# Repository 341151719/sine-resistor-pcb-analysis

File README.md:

# 正弦电阻 / Active Acoustic Impedance Controller

这是 PCB 修正、SPICE 分析和故障排查的审计仓库。仓库的目的，是让每次
电路修改、仿真假设和判断都能通过 Git 提交记录追溯；它不是已经通过生产
签核的最终硬件发布包。

## 先看什么

0. [新板从验收到初步改板操作手册](新板从验收到初步改板操作手册.md)：按新板版本确认、断电检查、基本上电、固件编写/烧录、问题复现和可逆改板的顺序执行。
1. [2026-09-15 实验还原证据复核](实验还原部分/主动审计/EVIDENCE_REASSESSMENT_20260915.md)：修正峰值电流与持续CC混淆，同步H07/H08状态，补充较大启动扰动验证。
2. [V8 KiCad 修正版](KICAD部分/正弦电阻V8_KiCad10.0.4_稳定性修正版_2026-09-04/)
   及其 [修改说明](KICAD部分/正弦电阻V8_KiCad10.0.4_稳定性修正版_2026-09-04/RELEASE_NOTES_V8.md)。
3. [V7 加工基线](KICAD部分/给厂商的板子加工数据/正弦电阻V7_KiCad10.0.4_校正转换版/)。
4. [SPICE 验证报告](SPICE部分/VALIDATION_REPORT_20260904.md) 和
   [实际问题记录](实际遇到的问题/)。
5. [故障假设排查总表](故障假设排查_20260908/假设总表.md)：H01–H11 记录
   单一加工/参数错误审计；H12 新增 OPA548 E/S–R5 组合动态机制审计。
6. [实验还原与可复现证据](实验还原部分/)：实板实验记录、早期错误复现和
   对既有 SPICE/KiCad 检查盲区的主动审计。

## 当前诊断状态（2026-09-08）

后续状态更新（2026-09-15）：H07修正版的3个固定偏置案例均完成且未复现目标，但不覆盖上电过程；
H08修正版未复现，但使用V8的C27值。OPA ON案例的约69 mA峰值不构成持续70 mA CC验证。
以下段落保留2026-09-08的模型结论，具体有效性以最新证据复核和更新后的假设总表为准。

官方 OPA548/OPA1656 模型在正确的 PSpice 兼容设置下可以运行。H12 进一步
解除此前“OPA548 固定 OFF”的假设，并加入 R10/TLP185、有限 E/S 状态和
J1/PGND 非理想项。23 组机制扫描没有自然产生 100--110 kHz；但当 OPA548
进入 ON 时，全官方模型出现约 453 kHz 的 U4B–R5–OPA548 组合模态，且把
R5 近似拆除后该模态消失。TP8 只有约 56 µVpp，因此仍不能解释实板上
100--110 kHz、超过 10 Vpp 的目标波形。H01–H11 的单点排查结论保持不变；
“本模型未复现”不等于已排除实物器件损坏、多故障叠加或未建模动态。

## 目录

| 目录 | 内容 |
|---|---|
| `KICAD部分/` | V7/V8 原理图、PCB、封装表、加工输出和验证记录 |
| `SPICE部分/` | SPICE 源模型、网表、脚本和历史验证报告 |
| `实际遇到的问题/` | 实测现象、局部网表和根因判定计划 |
| `故障假设排查_20260908/` | 每个假设独立存档的预测、deck、log 和审查 |
| `实验还原部分/` | 经整理的实板记录、可运行复现 deck 和主动审计脚本 |

## 复现约定

仿真通常使用 ngspice-42；TI PSpice 宏模型需要 `set ngbehavior=ps`，并且
某些官方模型需要显式 `TEMP`。每个故障目录都记录了实际命令和模型限制。
历史网表中可能保留当时机器的绝对路径，这是审计记录的一部分；在新机器
上运行前应根据目录位置调整 `.include` 路径。`.dat` 波形文件和环境安装包
没有纳入 Git，它们可由网表重新生成，避免仓库膨胀。

## 版本纪律

V7 目录作为原始加工基线保留；V8 是当前修正版工作状态，不应在没有新的
验证记录时覆盖。请用独立提交记录新的板改动、仿真假设和结论，并在
`CHANGELOG.md` 中补充面向人的摘要。

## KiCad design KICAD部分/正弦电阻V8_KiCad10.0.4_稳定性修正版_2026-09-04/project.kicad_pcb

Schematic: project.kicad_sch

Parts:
C1, C2: 10uF; C0805; LCSC Part # C15850
C3, C9, C10, C15, C16, C18, C19, C20, C21, C22, C26: 100nF; C0805; LCSC Part # C49678
C4: 47nF; C0805; LCSC Part # C1845663
C5, C6: 470uF; CAP-SMD_BD10.0-L10.3-W10.3-LS11.3-FD; Manufacturer Part XT470UF35V90RV0080; LCSC Part Name 470uF ±20% 35V
C7, C8: 100nF; C0805; Manufacturer Part CC0805KRX7R9BB104; LCSC Part Name 100nF ±10% 50V
C11, C12, C25, C28: 1uF; C0805; LCSC Part # C344178
C13, C14: 1p/2.2p/4.7p EXP; C0805; not fitted
C17: 10nF; C0805; LCSC Part # C342877
C23: 220nF; C0805; LCSC Part # C45359963
C24: 4.7uF; C0805; LCSC Part # C380342
C27: 10nF; C0805; Manufacturer Part C0805C103J5GACTU; LCSC Part # C2167597
C29, C30: 1uF; C0805; not fitted
C31, C37: 4.7p; C0805; not fitted
C32, C38: 10p; C0805; not fitted
C33, C39: 22p; C0805; not fitted
C34, C40: 47p; C0805; not fitted
C35, C41: 100p; C0805; not fitted
C36, C42: 10p-100p; C0805; not fitted
D1, D2: SS56B; SMB_L4.3-W3.6-LS5.4-RD; LCSC Part # C14651
D3: SS56 +clamp SPK DNP; SMB_L4.3-W3.6-LS5.4-RD; not fitted
D4: SS56 -clamp SPK DNP; SMB_L4.3-W3.6-LS5.4-RD; not fitted
FB1, FB2, FB3: 150R@100MHz; L0805; LCSC Part # C139474
FRAME1: default841x594
J1, J2, J5, J6: WAGO 2060 3P; CONN-SMD_2060-453; Manufacturer Part 2060-453/998-404; LCSC Part Name 1x3P 4mm 每排P数:3 排数:1
J3, J9: WAGO 2060 2P; CONN-SMD_2060-452; Manufacturer Part 2060-452/998-404; LCSC Part Name 1x2P 4mm 每排P数:2 排数:1
J4: WAGO 2060 2P; CONN-SMD_2060-452; Manufacturer Part SPEAKER WAGO 2060 SMT 2P; LCSC Part Name 1x2P 4mm 每排P数:2 排数:1
J7: SWD bare SMT pads; AAI_C11_35_LOCAL_Footprints_AAI_PinHeader_1x05_P1_27mm_Vert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
J8: WAGO 2060 3P; CONN-SMD_2060-453; Manufacturer Part UART bare SMT pads; LCSC Part Name 1x3P 4mm 每排P数:3 排数:1
J10: EXP_SPI_TIM_DNP; AAI_C11_35_LOCAL_Footprints_AAI_PinHeader_1x05_P2_54mm_Vert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; not fitted
J11: EXP_I2C_DAC_DNP; AAI_C11_35_LOCAL_Footprints_AAI_PinHeader_1x05_P2_54mm_Vert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; not fitted
J12, J13: 1×5P 2.54mm母排; HDR-TH_5P-P2.54-V-F; Manufacturer Part 2.54-1*5P母; LCSC Part Name 1x5P 间距:2.54mm 直插
J14: WAGO 2060 1P; CONN-SMD_L12.7-W3.9_2060-451-998-404; Manufacturer Part 2060-451/998-404; LCSC Part Name 1x1P 每排P数:1 排数:1
R1, R2, R42, R43: 0R; R0805; not fitted
R3, R4, R17, R36, R46: 0R; R0805; LCSC Part # C17477
R5, R18: 100R; R0805; LCSC Part # C2988937
R6: 0R; R0805; Manufacturer Part 0805W8F0000T5E; LCSC Part Name 0Ω ±1% 125mW 厚膜电阻
R7: 57.6kR; R0805; LCSC Part # C5153977
R8: 33.2kR 1%; R0805; not fitted
R9: 22.1kR 1%; R0805; not fitted
R10: 6.8kR; R0805; Manufacturer Part 0805W8F6801T5E; LCSC Part # C17772
R11: 1kR; R0805; LCSC Part # C95781
R12: 4.7R 2W; AAI_R_2512_Production_4R7_2W; Manufacturer Part CRH2512F4R70E04S; LCSC Part # C2897629
R13, R15: 1.000kR; R0805; LCSC Part # C110774
R14: 49.9kR; R0805; LCSC Part # C1730568
R16: 39.0kR; R0805; LCSC Part # C1720356
R19: 30.9kR; R0805; LCSC Part # C865394
R20, R21, R22, R35: 10.0kR; R0805; LCSC Part # C110775
R23: 100kR; R0805; LCSC Part # C2907217
R24: 10kR; R0805; LCSC Part # C2907219
R25: 6.49kR 0.1%; R0805; not fitted
R26, R31: 10k; R0805; not fitted
R27, R30: 100k; R0805; not fitted
R28: 100kR ±1%; R0805; not fitted
R29: 10kR ±1%; R0805; not fitted
R32, R33: 360kR ±1%; R0805; not fitted
R34: 1.000MR; R0805; LCSC Part # C2075448
R37, R38, R40: 1MR; R0805; not fitted
R39: 10kR; R0805; not fitted
R41: 10MR; R0805; not fitted
R44, R45: 1k-10k; R0805; not fitted
RSH2: 0.100R; AAI_C11_35_LOCAL_Footprints_AAI_SHUNT_4T_3920_Kelvin; LCSC Part # C393067
TP1: TP1; AAI_C11_35_LOCAL_Footprints_AAI_TestPoint_THTPad_D1_5mm_Dri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
TP2: TP2; AAI_C11_35_LOCAL_Footprints_AAI_TestPoint_THTPad_D1_5mm_Dri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
TP3: SENSE_DRV; AAI_C11_35_LOCAL_Footprints_AAI_TestPoint_THTPad_D1_5mm_Dri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
TP4: SENSE_SPK; AAI_C11_35_LOCAL_Footprints_AAI_TestPoint_THTPad_D1_5mm_Dri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
TP5: TP5; AAI_C11_35_LOCAL_Footprints_AAI_TestPoint_THTPad_D1_5mm_Dri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
TP6: TP6; AAI_C11_35_LOCAL_Footprints_AAI_TestPoint_THTPad_D1_5mm_Dri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
TP7: TP7; AAI_C11_35_LOCAL_Footprints_AAI_TestPoint_THTPad_D1_5mm_Dri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
TP8: TP8; AAI_C11_35_LOCAL_Footprints_AAI_TestPoint_THTPad_D1_5mm_Dri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
TP9: TP9; AAI_C11_35_LOCAL_Footprints_AAI_TestPoint_THTPad_D1_5mm_Dri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
TP10: TP10; AAI_C11_35_LOCAL_Footprints_AAI_TestPoint_THTPad_D1_5mm_Dri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
TP11: TP11; AAI_C11_35_LOCAL_Footprints_AAI_TestPoint_THTPad_D1_5mm_Dri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
TP12: TP12; AAI_C11_35_LOCAL_Footprints_AAI_TestPoint_THTPad_D1_5mm_Dri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
TP13: TP13; AAI_C11_35_LOCAL_Footprints_AAI_TestPoint_THTPad_D1_5mm_Dri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
TP14: TP14; AAI_C11_35_LOCAL_Footprints_AAI_TestPoint_THTPad_D1_5mm_Dri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
TP15: TP15; AAI_C11_35_LOCAL_Footprints_AAI_TestPoint_THTPad_D1_5mm_Dri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
TP16: TP16; AAI_C11_35_LOCAL_Footprints_AAI_TestPoint_THTPad_D1_5mm_Dri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
TP17: TP17; AAI_C11_35_LOCAL_Footprints_AAI_TestPoint_THTPad_D1_5mm_Dri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
TP18: TP_VSENSE_RAW; AAI_C11_35_LOCAL_Footprints_AAI_TestPoint_THTPad_D1_5mm_Dri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
TP19: TP_AD633_Z; AAI_C11_35_LOCAL_Footprints_AAI_TestPoint_THTPad_D1_5mm_Dri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
TP20: TP_IPORT; AAI_C11_35_LOCAL_Footprints_AAI_TestPoint_THTPad_D1_5mm_Dri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
TP21: Test-Point-0.5mm
U1: OPA548F/500; TO-263-7_L10.2-W10.4-P1.27-LS14.4-TL; Manufacturer Part OPA548F/500; LCSC Part Name 高压、大电流运算放大器
U2: AD633ARZ-R7; SOIC-8_L4.9-W3.9-P1.27-LS6.0-BL; Manufacturer Part AD633ARZ-R7; LCSC Part Name 四象限模拟乘法器
U3: INA149AIDR; SOIC-8_L4.9-W3.9-P1.27-LS6.0-BL; Manufacturer Part INA149AIDR; LCSC Part Name 高共模电压差分放大器
U4, U8: OPA1656IDR; SOIC-8_L4.9-W3.9-P1.27-LS6.0-BL; Manufacturer Part OPA1656IDR; LCSC Part Name 超低噪声、低失真、FET输入音频运算放大器
U5: STM32G431CBT6; LQFP-48_L7.0-W7.0-P0.50-LS9.0-BL; Manufacturer Part STM32G431CBT6; LCSC Part Name 带DSP和FPU的170MHz主流ARM Cortex-M4 MCU，具有12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
U6: AMS1117-3.3; SOT-223-3_L6.5-W3.4-P2.30-LS7.0-BR; LCSC Part # C6186
U7: TLP185(GR-TPR,E; SOP-6_4P-L3.7-W4.6-P2.54-LS7.0-BL; Manufacturer Part TLP185(GR-TPR,E; LCSC Part Name DC输入 隔离电压(rms):3750V
U9: OPA1656IDR; SOIC-8_L4.9-W3.9-P1.27-LS6.0-BL; not fitted
U10: TMUX7219DGKRQ1; VSSOP-8_L3.0-W3.0-P0.65-LS4.9-BL; not fitted

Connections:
$1N56724: U9.6 (-INB), U9.7 (OUTB)
$1N56728: R23.2, TP21.1, U10.5 (EN)
AD633_Z: R36.1, R37.2, R38.2, TP19.1, U2.4 (Z)
ADC_ISIG: R27.2, U5.8 (PA0)
ADC_PWR_N: R30.2, R31.1, U5.11 (PA3)
ADC_PWR_P: R28.2, R29.1, U5.10 (PA2)
ADC_SPK: R25.2, R26.1, U5.9 (PA1)
ADC_TEMP: J13.4, U5.16 (PB0)
AGND: C9.2, C10.2, C11.2, C12.2, C15.2, C16.2, C17.2, C18.2, C22.2, C23.2, C25.2, C28.2, C29.2, J2.2, J6.2, R3.2, R4.1, R13.2, R15.2, R20.2, R26.2, R36.2, R43.2, TP16.1, U2.2 (Y2), U2.8 (X2), U3.1 (REFB), U3.5 (REFA), U5.19 (VSSA), U9.3 (+INA), U9.5 (+INB), U10.3 (GND), U10.6 (SEL), U10.8 (S2)
ANA_N: C10.1, C12.1, C16.1, FB2.2, TP12.1, U2.3 (-VS), U3.4 (V-), U4.4 (V-), U8.4 (V-), U9.4 (V-), U10.7 (VSS)
ANA_N_EXT: FB2.1, J2.3, R2.2
ANA_P: C9.1, C11.1, C15.1, FB1.2, J6.3, TP11.1, U2.6 (+VS), U3.7 (V+), U4.8 (V+), U8.8 (V+), U9.8 (V+), U10.4 (VDD)
ANA_P_EXT: FB1.1, J2.1, R1.2
DAC_AUX_RAW: J11.5, R35.1, U5.13 (PA5)
DAC_BUF: R17.1, U8.1 (OUTA), U8.5 (+INB)
DAC_BUF_N: R17.2, U8.2 (-INA)
DAC_R_FILT: C17.1, R18.2, U8.3 (+INA)
DAC_R_RAW: R18.1, U5.12 (PA4)
DGND: C1.2, C2.2, C3.2, C19.2, C20.2, C21.2, C24.2, C26.2, J3.2, J7.5, J8.3, J9.2, J11.2, J13.5, R4.2, R29.2, R31.2, U5.23 (VSS), U5.35 (VSS), U5.47 (VSS), U6.1 (ADJ(GND)), U7.3 (CAT)
DRV: D1.2 (A), D2.1 (K), R12.1, R46.2, RSH2.1 (FORCE_DRV), TP2.1
FAULT_IN: J9.1, U5.17 (PB1)
GPIO_SPARE1: J12.1, U5.15 (PA7)
GPIO_SPARE2: J12.2, U5.22 (PB10)
GPIO_SPARE3: J12.3, U5.29 (PB15)
GPIO_SPARE4: J12.4, U5.28 (PB14)
GPIO_SPARE5: J12.5, U5.27 (PB13)
GPIO_SPARE6: J13.1, U5.26 (PB12)
GPIO_SPARE7: J13.2, U5.25 (PB11)
GPIO_SPARE8: J13.3, U5.46 (PB9)
I2C_SCL: J11.3, R33.1, U5.45 (PB8-BOOT0)
I2C_SDA: J11.4, R32.1, U5.44 (PB7)
ILIM_SET: R7.1, R8.1, R9.1, TP10.1, U1.3 (ILIM)
IPORT: C29.1, R39.2, R40.1, TP20.1
ISIG: C13.1, C31.1, C32.1, C33.1, C34.1, C35.1, R14.1, R27.1, R39.1, R44.1, TP5.1, U2.7 (X1), U4.1 (OUTA)
ISIG_TRIM: C28.1, R34.1, R35.2
MCU_OPA_EN: R11.1, U5.14 (PA6)
MUL_RAW: TP7.1, U2.5 (W), U4.5 (+INB)
NRST: C26.1, J7.4, R24.1, U5.7 (PG10-NRST)
OPA_EN_LED_A: R11.2, U7.1 (AN)
OPA_ES: R10.1, TP9.1, U1.7 (E/S), U7.4 (EMI)
OPA_IN_N: R6.2, U1.2 (VIN-)
OPA_IN_P: R5.2, U1.1 (VIN+)
OPA_OUT: R46.1, U1.6 (VO)
PGND: C4.2, C5.1, C6.2, C7.2, C8.1, J1.2, J4.2, R3.1, TP17.1
PWR_N: C6.1, C8.2, C27.2, D2.2 (A), D4.2 (A), J1.3, R2.1, R7.2, R8.2, R9.2, R10.2, R30.1, TP14.1, U1.4 (V-), U1.8 (V-)
PWR_P: C5.2, C7.1, C27.1, D1.1 (K), D3.1 (K), J1.1, R1.1, R28.1, TP13.1, U1.5 (V+), U7.6 (COL)
SENSE_DRV: RSH2.3 (SENSE_DRV), TP3.1, U3.2 (IN-)
SENSE_SPK: RSH2.4 (SENSE_SPK), TP4.1, U3.3 (IN+)
SERVO_INT_N: C30.2, R40.2, R41.2, R42.2, U9.2 (-INA), U10.2 (S1)
SNUB_MID: C4.1, R12.2
SPI_MISO: J10.3, U5.41 (PB4)
SPI_MOSI: J10.4, U5.42 (PB5)
SPI_NSS: J10.1, U5.39 (PA15)
SPI_SCK: J10.2, U5.40 (PB3)
SPK: D3.2 (A), D4.1 (K), J4.1, R6.1, R25.1, RSH2.2 (FORCE_SPK), TP1.1
SWCLK: J7.3, U5.38 (PA14)
SWDIO: J7.2, U5.37 (PA13)
TIM_SYNC: J10.5, U5.30 (PA8)
U4A_LEAD_MID: C36.1, R44.2
U4A_N: C13.2, C31.2, C32.2, C33.2, C34.2, C35.2, C36.2, R13.1, R14.2, R34.2, U4.2 (-INA)
U4B_LEAD_MID: C42.1, R45.2
U4B_N: C14.2, C37.2, C38.2, C39.2, C40.2, C41.2, C42.2, R15.1, R16.2, U4.6 (-INB)
UART_RX: J8.2, U5.32 (PA10)
UART_TX: J8.1, U5.31 (PA9)
V3V3: C2.1, C3.1, C19.1, C20.1, C21.1, C24.1, FB3.1, J7.1, J11.1, R23.1, R24.2, R32.2, R33.2, TP15.1, U5.1 (VBAT), U5.24 (VDD), U5.36 (VDD), U5.48 (VDD), U6.2 (VOUT), U6.4 (VOUT)
V3V3A: C22.1, C23.1, C25.1, FB3.2, R19.1, U5.20 (VREF+), U5.21 (VDDA)
V5_IN: C1.1, J3.1, U6.3 (VIN)
VCMD: C14.1, C37.1, C38.1, C39.1, C40.1, C41.1, R5.1, R16.1, R45.1, TP8.1, U4.7 (OUTB)
VK: J5.2, TP6.1, U2.1 (Y1)
VK_AMP_N: R21.1, R22.2, U8.6 (-INB)
VK_EXT: J5.3, J6.1
VK_MCU: J5.1, R22.1, U8.7 (OUTB)
VREF_0V477: C18.1, R19.2, R20.1, R21.2
VSENSE_RAW: TP18.1, U3.6 (VOUT), U4.3 (+INA)
ZSERVO_OUT: C30.1, R38.1, R41.1, R42.1, R43.1, U9.1 (OUTA), U10.1 (D)
ZTRIM: J14.1, J14.2, R37.1

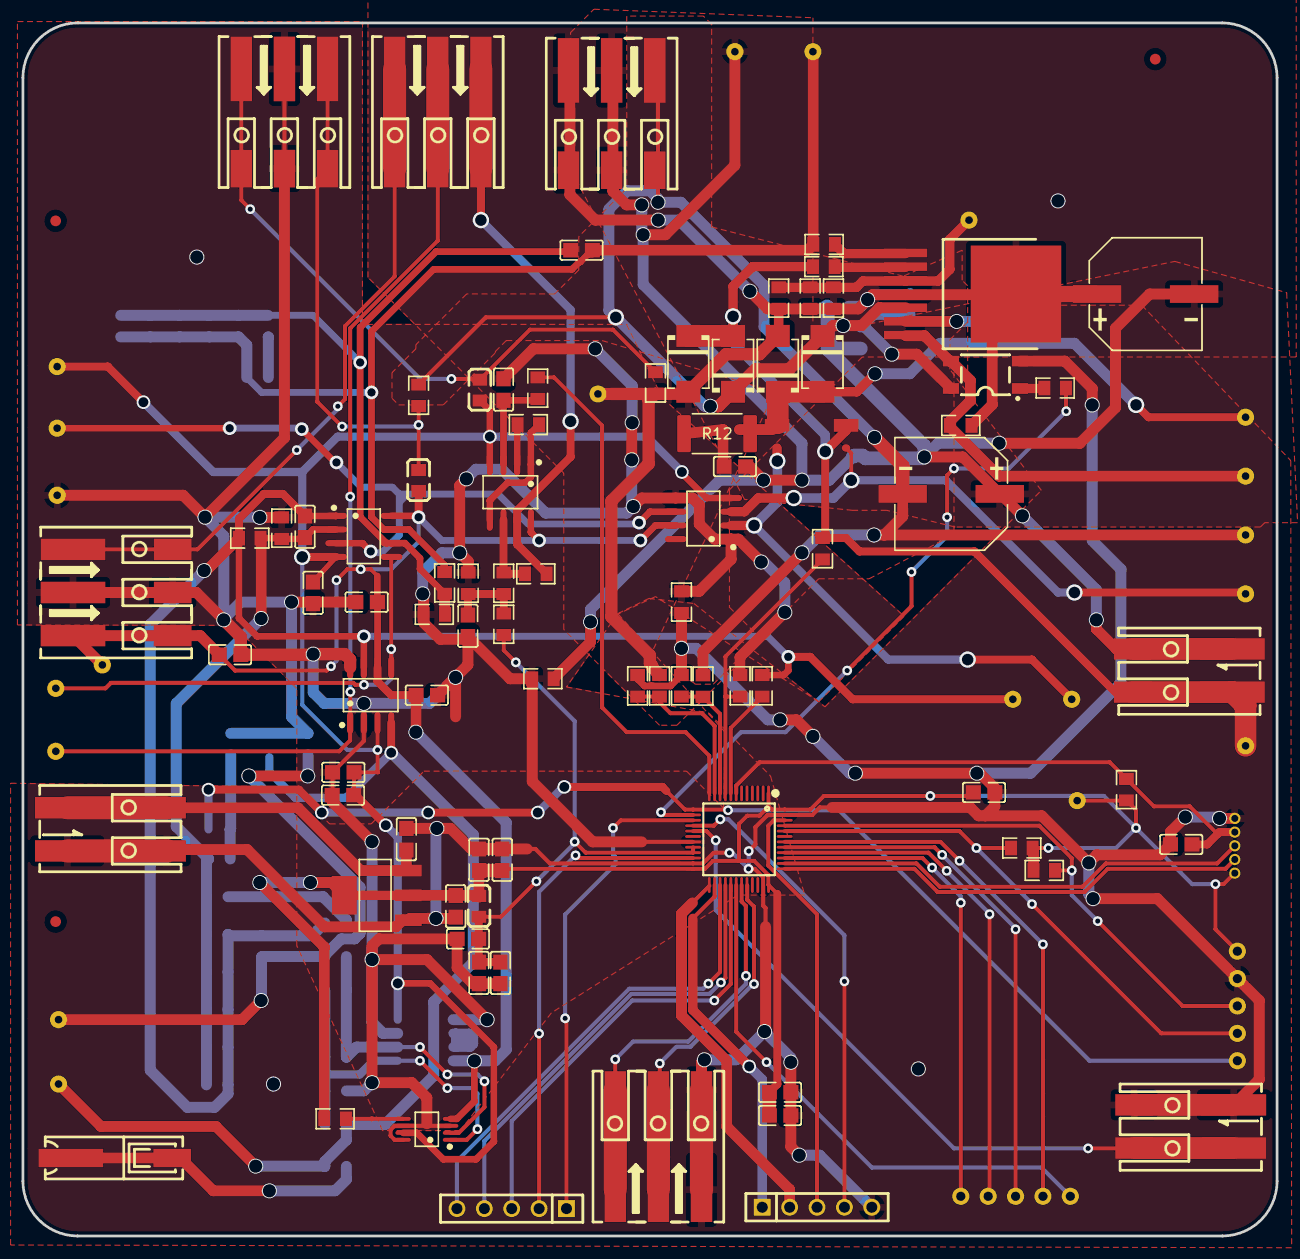
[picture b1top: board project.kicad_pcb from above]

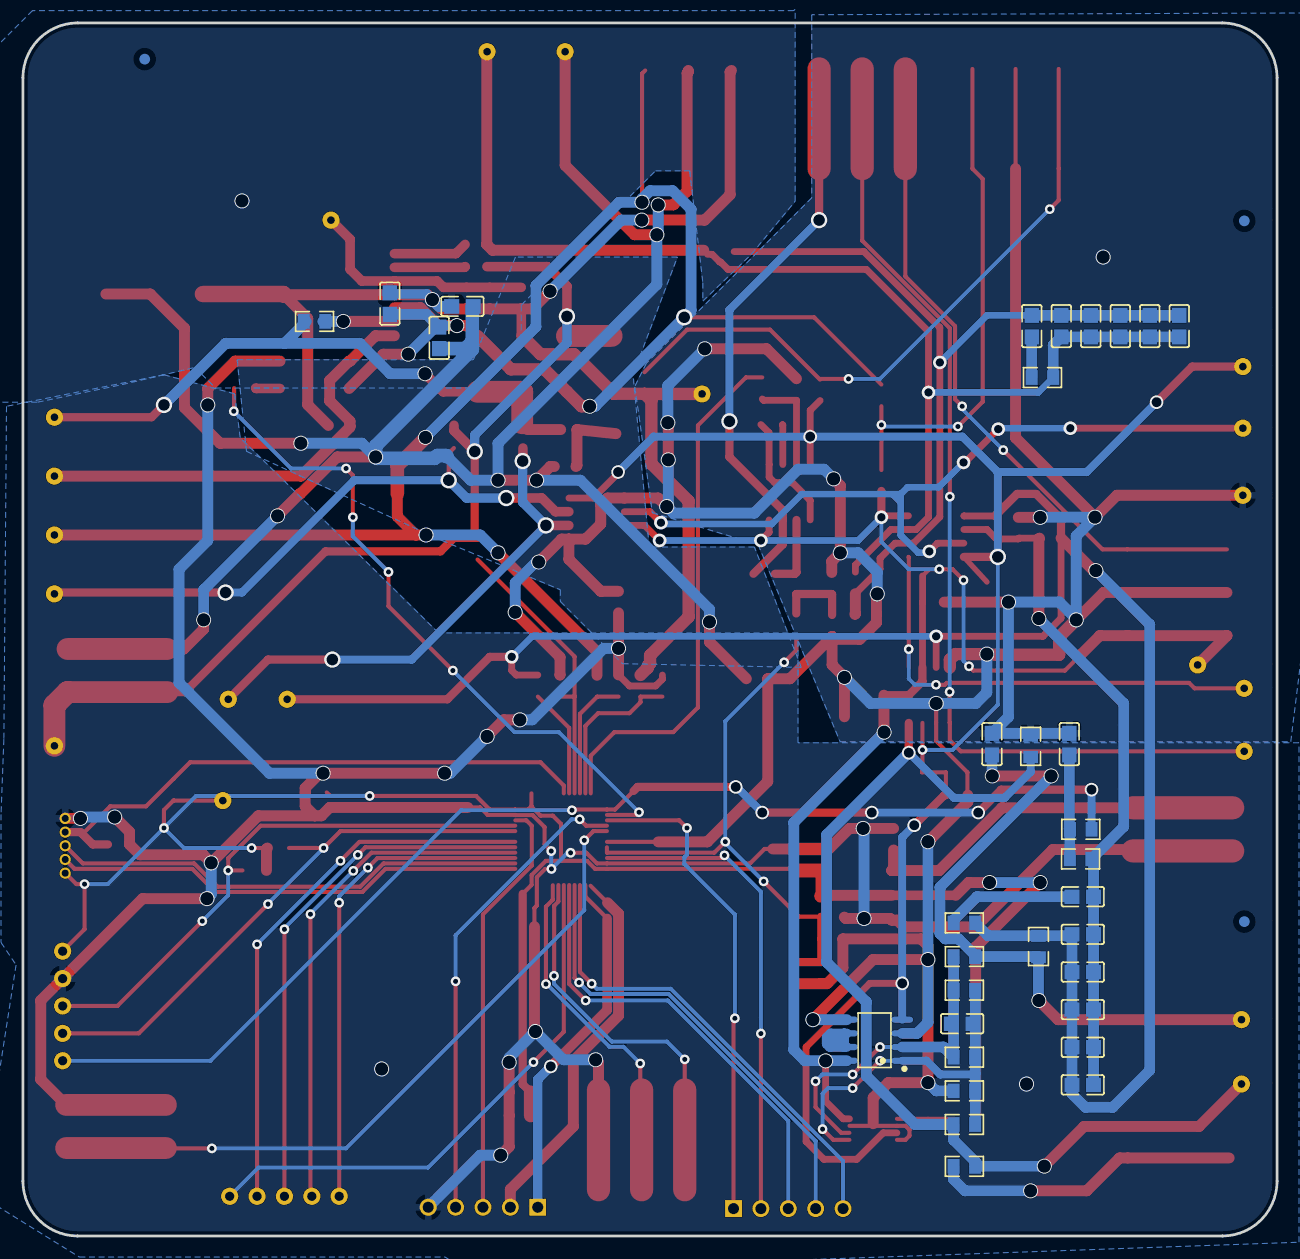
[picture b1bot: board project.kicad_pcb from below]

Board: 2 copper layers, 116.3 x 112.5 mm, 147 parts (35 on the bottom side), 76 nets.

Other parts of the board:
FID1, FID2, FID3: Fiducial; AAI_Fiducial_1mm_Mask2mm
FID4, FID5, FID6: Fiducial; AAI_Fiducial_1mm_Mask2mm_Bottom

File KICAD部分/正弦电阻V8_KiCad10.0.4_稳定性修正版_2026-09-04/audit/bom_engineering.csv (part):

"Refs","Value","Footprint","Qty","DNP","Assembly Status","LCSC Part #","BOM Value"
"C1","10uF","easyedapro:C0805","1","","SMT","C15850","10µF ±10% 25V X5R"
"C2","10uF","easyedapro:C0805","1","","SMT","C15850","10µF ±10% 25V X5R"
"C3","100nF","easyedapro:C0805","1","","SMT","C49678","100nF ±10% 50V X7R"
"C4","47nF","easyedapro:C0805","1","","SMT","C1845663","47nF ±5% 50V X7R"
"C5","470uF","easyedapro:CAP-SMD_BD10.0-L10.3-W10.3-LS11.3-FD","1","","SMT","C2992611","470µF ±20% 35V, 105°C"
"C6","470uF","easyedapro:CAP-SMD_BD10.0-L10.3-W10.3-LS11.3-FD","1","","SMT","C2992611","470µF ±20% 35V, 105°C"
"C7","100nF","easyedapro:C0805","1","","SMT","C49678","100nF ±10% 50V X7R"
"C8","100nF","easyedapro:C0805","1","","SMT","C49678","100nF ±10% 50V X7R"
"C9","100nF","easyedapro:C0805","1","","SMT","C49678","100nF ±10% 50V X7R"
"C10","100nF","easyedapro:C0805","1","","SMT","C49678","100nF ±10% 50V X7R"
"C11","1uF","easyedapro:C0805","1","","SMT","C344178","1µF ±10% 50V X7R"
"C12","1uF","easyedapro:C0805","1","","SMT","C344178","1µF ±10% 50V X7R"
"C13","1p/2.2p/4.7p EXP","easyedapro:C0805","1","DNP","DNP","","DNP；实验备料1pF/2.2pF/4.7pF C0G 0805"
"C14","1p/2.2p/4.7p EXP","easyedapro:C0805","1","DNP","DNP","","DNP；实验备料1pF/2.2pF/4.7pF C0G 0805"
"C15","100nF","easyedapro:C0805","1","","SMT","C49678","100nF ±10% 50V X7R"
"C16","100nF","easyedapro:C0805","1","","SMT","C49678","100nF ±10% 50V X7R"
"C17","10nF","easyedapro:C0805","1","","SMT","C342877","10nF ±5% 50V C0G"
"C18","100nF","easyedapro:C0805","1","","SMT","C49678","100nF ±10% 50V X7R"
"C19","100nF","easyedapro:C0805","1","","SMT","C49678","100nF ±10% 50V X7R"
"C20","100nF","easyedapro:C0805","1","","SMT","C49678","100nF ±10% 50V X7R"
"C21","100nF","easyedapro:C0805","1","","SMT","C49678","100nF ±10% 50V X7R"
"C22","100nF","easyedapro:C0805","1","","SMT","C49678","100nF ±10% 50V X7R"
"C23","220nF","easyedapro:C0805","1","","SMT","C45359963","220nF ±10% 50V X7R"
"C24","4.7uF","easyedapro:C0805","1","","SMT","C380342","4.7µF ±10% 16V X5R"
"C25","1uF","easyedapro:C0805","1","","SMT","C344178","1µF ±10% 50V X7R"
"C26","100nF","easyedapro:C0805","1","","SMT","C49678","100nF ±10% 50V X7R"
"C27","10pF","easyedapro:C0805","1","","SMT","C157608","10pF ±5% 50V C0G"
"C28","1uF","easyedapro:C0805","1","","SMT","C344178","1µF ±10% 50V X7R"
"C29","1uF","easyedapro:C0805","1","DNP","DNP","","1uF"
"C30","1uF","easyedapro:C0805","1","DNP","DNP","","1uF"
"C31","4.7p","easyedapro:C0805","1","DNP","DNP","","4.7p"
"C32","10p","easyedapro:C0805","1","DNP","DNP","","10p"
"C33","22p","easyedapro:C0805","1","DNP","DNP","","22p"
"C34","47p","easyedapro:C0805","1","DNP","DNP","","47p"
"C35","100p","easyedapro:C0805","1","DNP","DNP","","100p"
"C36","10p-100p","easyedapro:C0805","1","DNP","DNP","","10p-100p"
"C37","4.7p","easyedapro:C0805","1","DNP","DNP","","4.7p"
"C38","10p","easyedapro:C0805","1","DNP","DNP","","10p"
"C39","22p","easyedapro:C0805","1","DNP","DNP","","22p"
"C40","47p","easyedapro:C0805","1","DNP","DNP","","47p"
"C41","100p","easyedapro:C0805","1","DNP","DNP","","100p"
"C42","10p-100p","easyedapro:C0805","1","DNP","DNP","","10p-100p"
"D1","SS56B","easyedapro:SMB_L4.3-W3.6-LS5.4-RD","1","","SMT","C14651","SS56B, 60V 5A Schottky"
"D2","SS56B","easyedapro:SMB_L4.3-W3.6-LS5.4-RD","1","","SMT","C14651","SS56B, 60V 5A Schottky"
"D3","SS56 +clamp SPK DNP","easyedapro:SMB_L4.3-W3.6-LS5.4-RD","1","DNP","DNP","","SS56 +clamp SPK DNP"
"D4","SS56 -clamp SPK DNP","easyedapro:SMB_L4.3-W3.6-LS5.4-RD","1","DNP","DNP","","SS56 -clamp SPK DNP"
"FB1","150R@100MHz","easyedapro:L0805","1","","SMT","C139474","150Ω@100MHz, 600mA, DCR 0.25Ω"
"FB2","150R@100MHz","easyedapro:L0805","1","","SMT","C139474","150Ω@100MHz, 600mA, DCR 0.25Ω"
"FB3","150R@100MHz","easyedapro:L0805","1","","SMT","C139474","150Ω@100MHz, 600mA, DCR 0.25Ω"
"J1","WAGO 2060 3P","easyedapro:CONN-SMD_2060-453","1","","SMT","C2765056","WAGO 2060 3P, 4mm pitch"
"J2","WAGO 2060 3P","easyedapro:CONN-SMD_2060-453","1","","SMT","C2765056","WAGO 2060 3P, 4mm pitch"
"J3","WAGO 2060 2P","easyedapro:CONN-SMD_2060-452","1","","SMT","C2765055","WAGO 2060 2P, 4mm pitch"
"J4","WAGO 2060 2P","easyedapro:CONN-SMD_2060-452","1","","SMT","C2765055","WAGO 2060 2P, 4mm pitch"
"J5","WAGO 2060 3P","easyedapro:CONN-SMD_2060-453","1","","SMT","C2765056","WAGO 2060 3P, 4mm pitch"
"J6","WAGO 2060 3P","easyedapro:CONN-SMD_2060-453","1","","SMT","C2765056","WAGO 2060 3P, 4mm pitch"
"J8","WAGO 2060 3P","easyedapro:CONN-SMD_2060-453","1","","SMT","C2765056","WAGO 2060 3P, 4mm pitch"
"J9","WAGO 2060 2P","easyedapro:CONN-SMD_2060-452","1","","SMT","C2765055","WAGO 2060 2P, 4mm pitch"
"J10","EXP_SPI_TIM_DNP","easyedapro:AAI_C11_35_LOCAL_Footprints_AAI_PinHeader_1x05_P2_54mm_Vertical","1","DNP","DNP","","EXP_SPI_TIM_DNP"
"J11","EXP_I2C_DAC_DNP","easyedapro:AAI_C11_35_LOCAL_Footprints_AAI_PinHeader_1x05_P2_54mm_Vertical","1","DNP","DNP","","EXP_I2C_DAC_DNP"
"J12","1×5P 2.54mm母排","easyedapro:HDR-TH_5P-P2.54-V-F","1","","POST","C50950","1×5P 2.54mm母排"
"J13","1×5P 2.54mm母排","easyedapro:HDR-TH_5P-P2.54-V-F","1","","POST","C50950","1×5P 2.54mm母排"
"J14","WAGO 2060 1P","easyedapro:CONN-SMD_L12.7-W3.9_2060-451-998-404","1","","SMT","C2765054","WAGO 2060 1P, 4mm pitch"
"R1","0R","easyedapro:R0805","1","DNP","DNP","","0R"
"R2","0R","easyedapro:R0805","1","DNP","DNP","","0R"
"R3","0R","easyedapro:R0805","1","","SMT","C17477","0Ω 125mW"
"R4","0R","easyedapro:R0805","1","","SMT","C17477","0Ω 125mW"
"R5","100R","easyedapro:R0805","1","","SMT","C2988937","100Ω ±1% 125mW"
"R6","0R","easyedapro:R0805","1","","SMT","C17477","0Ω 125mW"
"R7","57.6kR","easyedapro:R0805","1","","SMT","C5153977","57.6kΩ ±1% 125mW"
"R8","33.2kR 1%","easyedapro:R0805","1","DNP","DNP","","33.2kΩ 1%"
"R9","22.1kR 1%","easyedapro:R0805","1","DNP","DNP","","22.1kΩ 1%"
"R10","100kR","easyedapro:R0805","1","","SMT","C2907217","100kΩ ±1% 125mW"
"R11","1kR","easyedapro:R0805","1","","SMT","C95781","1kΩ ±1% 125mW"
"R12","4.7R","easyedapro:R0805","1","","SMT","C2897629","4.7Ω ±1% 2W"
"R13","1.000kR","easyedapro:R0805","1","","SMT","C110774","1.000kΩ ±0.1% 薄膜"
"R14","49.9kR","easyedapro:R0805","1","","SMT","C1730568","49.9kΩ ±0.05% 15ppm/°C"
"R15","1.000kR","easyedapro:R0805","1","","SMT","C110774","1.000kΩ ±0.1% 薄膜"
"R16","39.0kR","easyedapro:R0805","1","","SMT","C1720356","39.0kΩ ±0.1% 10ppm/°C 200mW"
"R17","0R","easyedapro:R0805","1","","SMT","C17477","0Ω 125mW"
"R18","100R","easyedapro:R0805","1","","SMT","C2988937","100Ω ±1% 125mW"
"R19","30.9kR","easyedapro:R0805","1","","SMT","C865394","30.9kΩ ±0.1% ≤25ppm/°C 薄膜"
"R20","10.0kR","easyedapro:R0805","1","","SMT","C110775","10.0kΩ ±0.1% 薄膜"
"R21","10.0kR","easyedapro:R0805","1","","SMT","C110775","10.0kΩ ±0.1% 薄膜"
"R22","10.0kR","easyedapro:R0805","1","","SMT","C110775","10.0kΩ ±0.1% 薄膜"
"R23","100kR","easyedapro:R0805","1","","SMT","C2907217","100kΩ ±1% 125mW"
"R24","10kR","easyedapro:R0805","1","","SMT","C2907219","10kΩ ±1% 125mW"
"R25","6.49kR 0.1%","easyedapro:R0805","1","DNP","DNP","","6.49kΩ 0.1%"
"R26","10k","easyedapro:R0805","1","DNP","DNP","","10k"
"R27","100k","easyedapro:R0805","1","DNP","DNP","","100k"
"R28","100kR ±1%","easyedapro:R0805","1","DNP","DNP","","100kΩ ±1%"
"R29","10kR ±1%","easyedapro:R0805","1","DNP","DNP","","10kΩ ±1%"
"R30","100k","easyedapro:R0805","1","DNP","DNP","","100k"
"R31","10k","easyedapro:R0805","1","DNP","DNP","","10k"
"R32","360kR ±1%","easyedapro:R0805","1","DNP","DNP","","360kΩ ±1%"
"R33","360kR ±1%","easyedapro:R0805","1","DNP","DNP","","360kΩ ±1%"
"R34","1.000MR","easyedapro:R0805","1","","SMT","C2075448","1.000MΩ ±0.1% 25ppm/°C"
"R35","10.0kR","easyedapro:R0805","1","","SMT","C110775","10.0kΩ ±0.1% ≤25ppm/°C 薄膜"
"R36","0R","easyedapro:R0805","1","","SMT","C17477","0Ω 125mW"
"R37","1MR","easyedapro:R0805","1","DNP","DNP","","1MΩ"
"R38","1MR","easyedapro:R0805","1","DNP","DNP","","1MΩ"
"R39","10kR","easyedapro:R0805","1","DNP","DNP","","10kΩ"
"R40","1MR","easyedapro:R0805","1","DNP","DNP","","1MΩ"
"R41","10MR","easyedapro:R0805","1","DNP","DNP","","10MΩ"
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
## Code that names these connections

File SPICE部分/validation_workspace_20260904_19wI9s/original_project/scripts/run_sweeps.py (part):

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    return str(x).replace("-", "m").replace(".", "p").replace("+", "")


def mapping(spk: SpeakerTS, cfg: SimConfig, datafile: str) -> dict[str, str]:
    d = {k: sf(v) for k, v in asdict(spk).items()}
    d.update({k: sf(v) for k, v in asdict(cfg).items()})
    d["DATAFILE"] = datafile
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
def render(template: str, spk: SpeakerTS, cfg: SimConfig, datafile: str) -> str:
    txt = template
    for k, v in mapping(spk, cfg, datafile).items():
        txt = txt.replace(f"__{k}__", v)
    if "__" in txt:
        raise ValueError("Unreplaced template marker remains in rendered netlist")
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
def least_squares_reff(df: pd.DataFrame, spk: SpeakerTS, tail: pd.Series) -> tuple[float, float, int]:
    """Return total effective resistance Re + Rx_fit from Vspk ≈ Rx_fit*Iport."""
    ip = df.loc[tail, "v(iport)"].to_numpy(float)
    v = df.loc[tail, "v(spk)"].to_numpy(float)
    finite_mask = np.isfinite(ip) & np.isfinite(v)
    ip = ip[finite_mask]
    v = v[finite_mask]
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        "rx_cmd_min_ohm": amin(df["v(rxnode)"]),
        "rx_cmd_max_ohm": amax(df["v(rxnode)"]),
        "iport_pk_a": amax(np.abs(df["v(iport)"])),
        "iport_pk_tail_a": amax(np.abs(df.loc[tail, "v(iport)"])),
        "iport_threshold_for_reff_a": float(df["iport_threshold_for_reff"].iloc[0]),
        "vspk_pk_v": amax(np.abs(df["v(spk)"])),
        "vspk_pk_tail_v": amax(np.abs(df.loc[tail, "v(spk)"])),
        "vel_pk_mps": amax(np.abs(df["v(vel)"])),
        "x_pk_m": amax(np.abs(df["v(xnode)"])),
        "xmax_ratio_pk": amax(df["v(xmaxabs)"]),
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        qlo=2, qhi=98, pad=0.08, min_span=5,
    )

    axes[1].plot(t, df["v(spk)"], label="SPK")
    if "v(drv)" in df.columns:
        axes[1].plot(t, df["v(drv)"], label="DRV", alpha=0.8)
    if "v(vcmd)" in df.columns:
        axes[1].plot(t, df["v(vcmd)"], label="VCMD", alpha=0.8)
    if "rx_iport_v" in df.columns:
        axes[1].plot(t, df["rx_iport_v"], "--", label="Rx*Iport", alpha=0.8)
    axes[1].set_ylabel("V")
    axes[1].legend(ncol=4, fontsize=8)
    _apply_ylim(axes[1], [df.get("v(spk)"), df.get("v(drv)"), df.get("v(vcmd)"), df.get("rx_iport_v")], qlo=1, qhi=99, pad=0.12, min_span=1e-4, symmetric=True)

    axes[2].plot(t, df["v(iport)"], label="Iport")
    thr = float(df["iport_threshold_for_reff"].iloc[0]) if "iport_threshold_for_reff" in df.columns else None
    if thr and math.isfinite(thr):
        axes[2].axhline(thr, ls=":", lw=0.8, alpha=0.5)
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
    err_series = []
    if "v(synerr)" in df.columns:
        axes[3].plot(t, df["v(synerr)"], label="SPK - Rx*Iport")
        err_series.append(df["v(synerr)"])
    if "v(cmderr)" in df.columns:
        axes[3].plot(t, df["v(cmderr)"], label="VCMD - Rx*Iport", alpha=0.8)
        err_series.append(df["v(cmderr)"])
    if "v(followerr)" in df.columns:
        axes[3].plot(t, df["v(followerr)"], label="VCMD - SPK", alpha=0.65)
        err_series.append(df["v(followerr)"])
    axes[3].set_ylabel("error V")
    axes[3].legend(ncol=3, fontsize=8)
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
